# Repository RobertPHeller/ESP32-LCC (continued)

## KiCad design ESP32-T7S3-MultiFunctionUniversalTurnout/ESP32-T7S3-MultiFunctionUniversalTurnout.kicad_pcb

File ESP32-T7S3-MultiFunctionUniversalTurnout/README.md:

# ESP32-T7S3-MultiFunctionUniversalTurnout

This is a LCC node circuit board that is based around an Lily Go TTGO-T7S3
(Mini32) board to manage and operate a collection of model railroad sensors and
actuators. 

The board contains these I/O sections:

- Four occupancy detectors. CT Coil type sensors, so they won't work with DC
systems without an AC bias.
- Four turnout drivers with point sense.  These are on a daughter board.  There
are four daughter board types: one for stall motors (Tortoise and the like),
one for single-coil motors (Kato), one for twin-coil motors (Atlas, Peco), and
one for servos.
- Four Schmitt Trigger inputs, meant for push buttons.
- Four Buffered outputs, by default for Panel LEDS, but with drop in
resistors, can also drive relays or other loads.
- Sixteen PWM Led drivers. These are meant to light (LED) lamps in signal
heads.

The board connects to a LCC network and utilizes the Event Transport Protocol
in its operation. It also uses a CDI to describe its configuration. It can be
configured with JMRI or other available LCC configuration tools.

The board draws about 100ma, plus load. There are 16 signal lamp outputs that
have 1.5K Ohm load resistors, this means about 8ma per LED. If all lamps are
on at full brightness, this comes to 128ma, although turning all 16 signal
lamps on full at a time is not likely to be prototypical, since most signal
aspects only light one lamp per head. There is a terminal block to optionally
supply external power for the signal lamps, as a way to reduce the load on the
LCC power bus. The buffered output section uses an external power source, so
does not add any load to the LCC power bus.

This board is a multi-purpose board that can be used in a number of
situations, including (but not limited to): one end of a siding, a yard or
terminal throat, ABS, and interlocking plants.</p>

## Firmware

The firmware for this board is [ESP32-S3-MultiFunctionOpenMRNIDF](https://github.com/RobertPHeller/ESP32-LCC/tree/master/ESP32-S3-MultiFunctionOpenMRNIDF).

## Kit booket

There is LaTeX source for the kit booklet in [KitBooklet](https://github.com/RobertPHeller/ESP32-LCC/tree/master/ESP32-T7S3-MultiFunctionUniversalTurnout/KitBooklet).

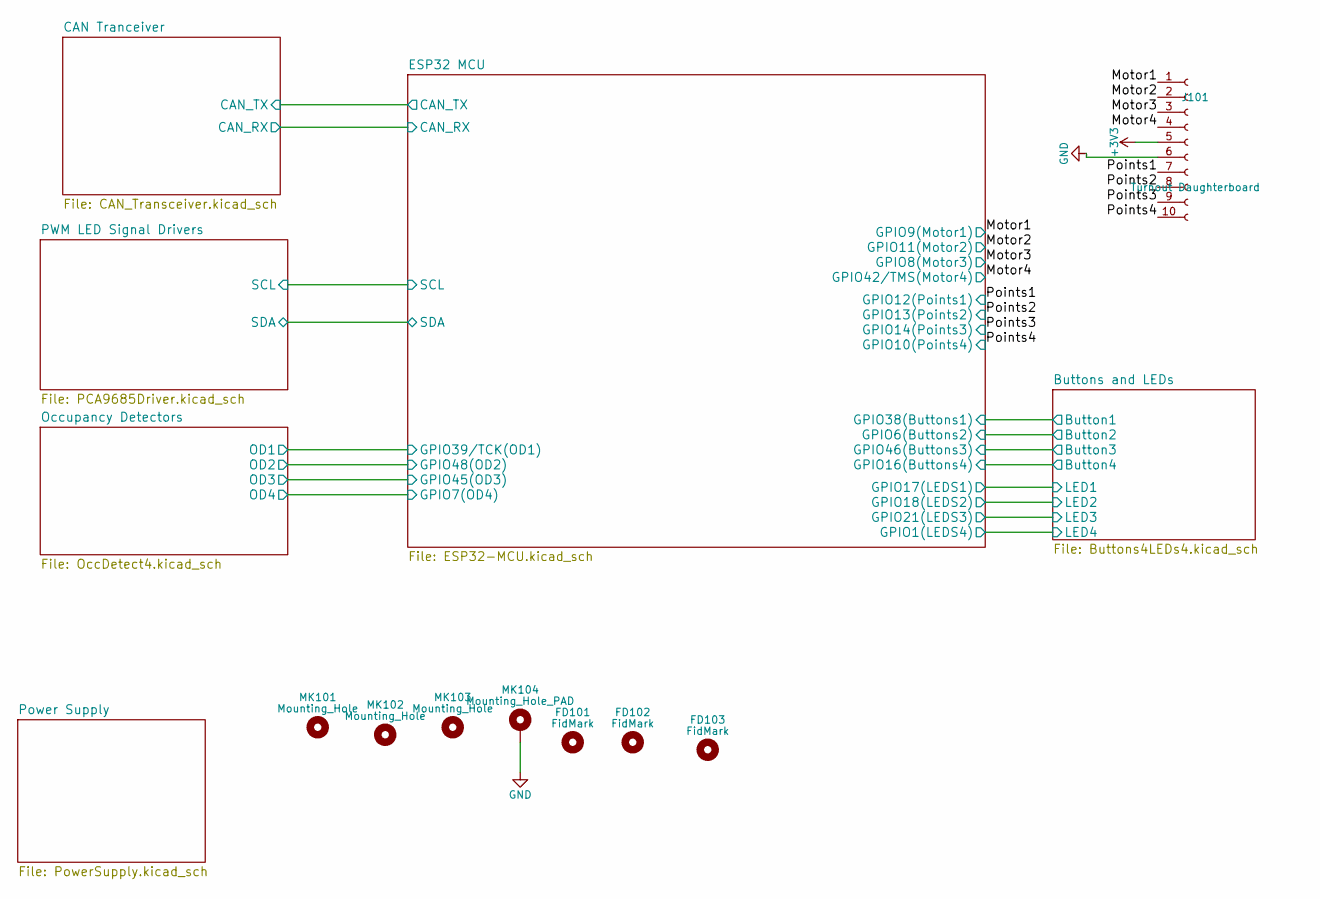
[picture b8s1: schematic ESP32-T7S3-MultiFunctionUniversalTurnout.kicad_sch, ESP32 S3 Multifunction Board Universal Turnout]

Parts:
FD101, FD102, FD103: FidMark; Fiducial_classic_Small_SilkscreenTop_Type1
J101: Turnout Daughterboard; Socket_Strip_Straight_1x10_Pitch2.54mm
MK101, MK102, MK103: Mounting_Hole; MountingHole_3.7mm
MK104: Mounting_Hole_PAD; MountingHole_3.7mm_Pad

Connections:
/Motor1: J101.1; also elsewhere on the board
/Motor2: J101.2; also elsewhere on the board
/Motor3: J101.3; also elsewhere on the board
/Motor4: J101.4; also elsewhere on the board
/Points1: J101.7; also elsewhere on the board
/Points2: J101.8; also elsewhere on the board
/Points3: J101.9; also elsewhere on the board
/Points4: J101.10; also elsewhere on the board
GND: J101.6, MK104.1; also elsewhere on the board

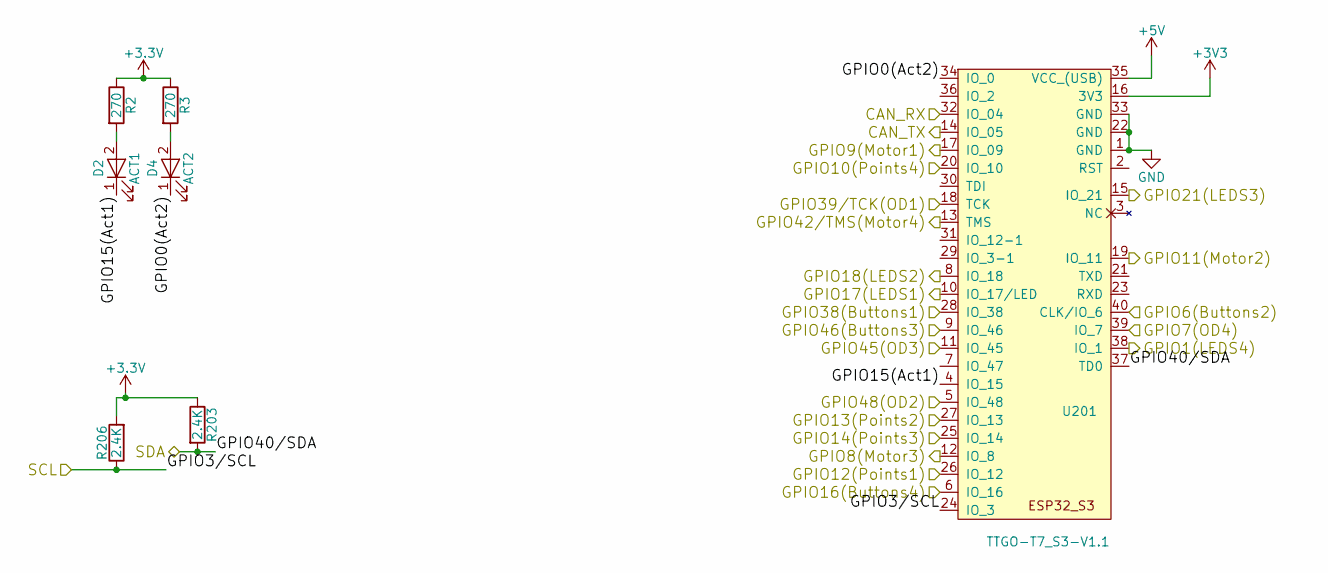
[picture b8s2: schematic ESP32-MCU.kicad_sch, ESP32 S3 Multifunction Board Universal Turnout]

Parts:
D2: ACT1; LED_0402; Mouser Part Number 710-150040GS73220
D4: ACT2; LED_0402; Mouser Part Number 710-150040SS73220
R2, R3: 270; R_0402; Mouser Part Number 754-RR0510P-271D
R203, R206: 2.4K; R_0402; Mouser Part Number 603-RC0402FR-072K4L
U201: TTGO-T7_S3-V1.1; ESP32_mini

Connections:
+5V: U201.35 (VCC_(USB)); also elsewhere on the board
/Buttons and LEDs/Button1: U201.28 (IO_38); also elsewhere on the board
/Buttons and LEDs/Button2: U201.40 (CLK/IO_6); also elsewhere on the board
/Buttons and LEDs/Button3: U201.9 (IO_46); also elsewhere on the board
/Buttons and LEDs/Button4: U201.6 (IO_16); also elsewhere on the board
/Buttons and LEDs/LED1: U201.10 (IO_17/LED); also elsewhere on the board
/Buttons and LEDs/LED2: U201.8 (IO_18); also elsewhere on the board
/Buttons and LEDs/LED3: U201.15 (IO_21); also elsewhere on the board
/Buttons and LEDs/LED4: U201.38 (IO_1); also elsewhere on the board
/CAN Tranceiver/CAN_RX: U201.32 (IO_04); also elsewhere on the board
/CAN Tranceiver/CAN_TX: U201.14 (IO_05); also elsewhere on the board
/ESP32 MCU/GPIO0(Act2): D4.1 (K), U201.34 (IO_0)
/ESP32 MCU/GPIO3/SCL: R206.1, U201.24 (IO_3); also elsewhere on the board
/ESP32 MCU/GPIO7(OD4): U201.39 (IO_7); also elsewhere on the board
/ESP32 MCU/GPIO15(Act1): D2.1 (K), U201.4 (IO_15)
/ESP32 MCU/GPIO39/TCK(OD1): U201.18 (TCK); also elsewhere on the board
/ESP32 MCU/GPIO40/SDA: R203.2, U201.37 (TD0); also elsewhere on the board
/ESP32 MCU/GPIO45(OD3): U201.11 (IO_45); also elsewhere on the board
/ESP32 MCU/GPIO48(OD2): U201.5 (IO_48); also elsewhere on the board
/Motor1: U201.17 (IO_09); also elsewhere on the board
/Motor2: U201.19 (IO_11); also elsewhere on the board
/Motor3: U201.12 (IO_8); also elsewhere on the board
/Motor4: U201.13 (TMS); also elsewhere on the board
/Points1: U201.26 (IO_12); also elsewhere on the board
/Points2: U201.27 (IO_13); also elsewhere on the board
/Points3: U201.25 (IO_14); also elsewhere on the board
/Points4: U201.20 (IO_10); also elsewhere on the board
GND: U201.1 (GND), U201.22 (GND), U201.33 (GND); also elsewhere on the board
unnamed: D2.2 (A), R2.2
unnamed: D4.2 (A), R3.2

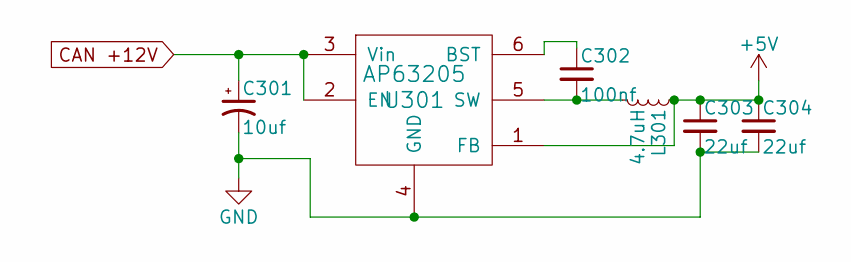
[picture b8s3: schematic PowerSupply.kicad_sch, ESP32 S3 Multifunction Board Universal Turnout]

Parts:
C301: 10uf; CP_Elec_5x5.3; Mouser Part Number 710-865230542002
C302: 100nf; C_0603; Mouser Part Number 710-885012206020
C303, C304: 22uf; C_0603; Mouser Part Number 603-CC0603MRX6S5B226
L301: 4.7uH; L_7.3x7.3_H4.5; Mouser Part Number 81-B1047AS-4R7N=P3
U301: AP63205; TSOT-23-6_MK06A; Mouser Part Number 621-AP63205WU-7

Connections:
+5V: C303.1, C304.1, L301.1, U301.1 (FB); also elsewhere on the board
CAN +12V: C301.1, U301.2 (EN), U301.3 (Vin); also elsewhere on the board
GND: C301.2, C303.2, C304.2, U301.4 (GND); also elsewhere on the board
unnamed: C302.1, U301.6 (BST)
unnamed: C302.2, L301.2, U301.5 (SW)

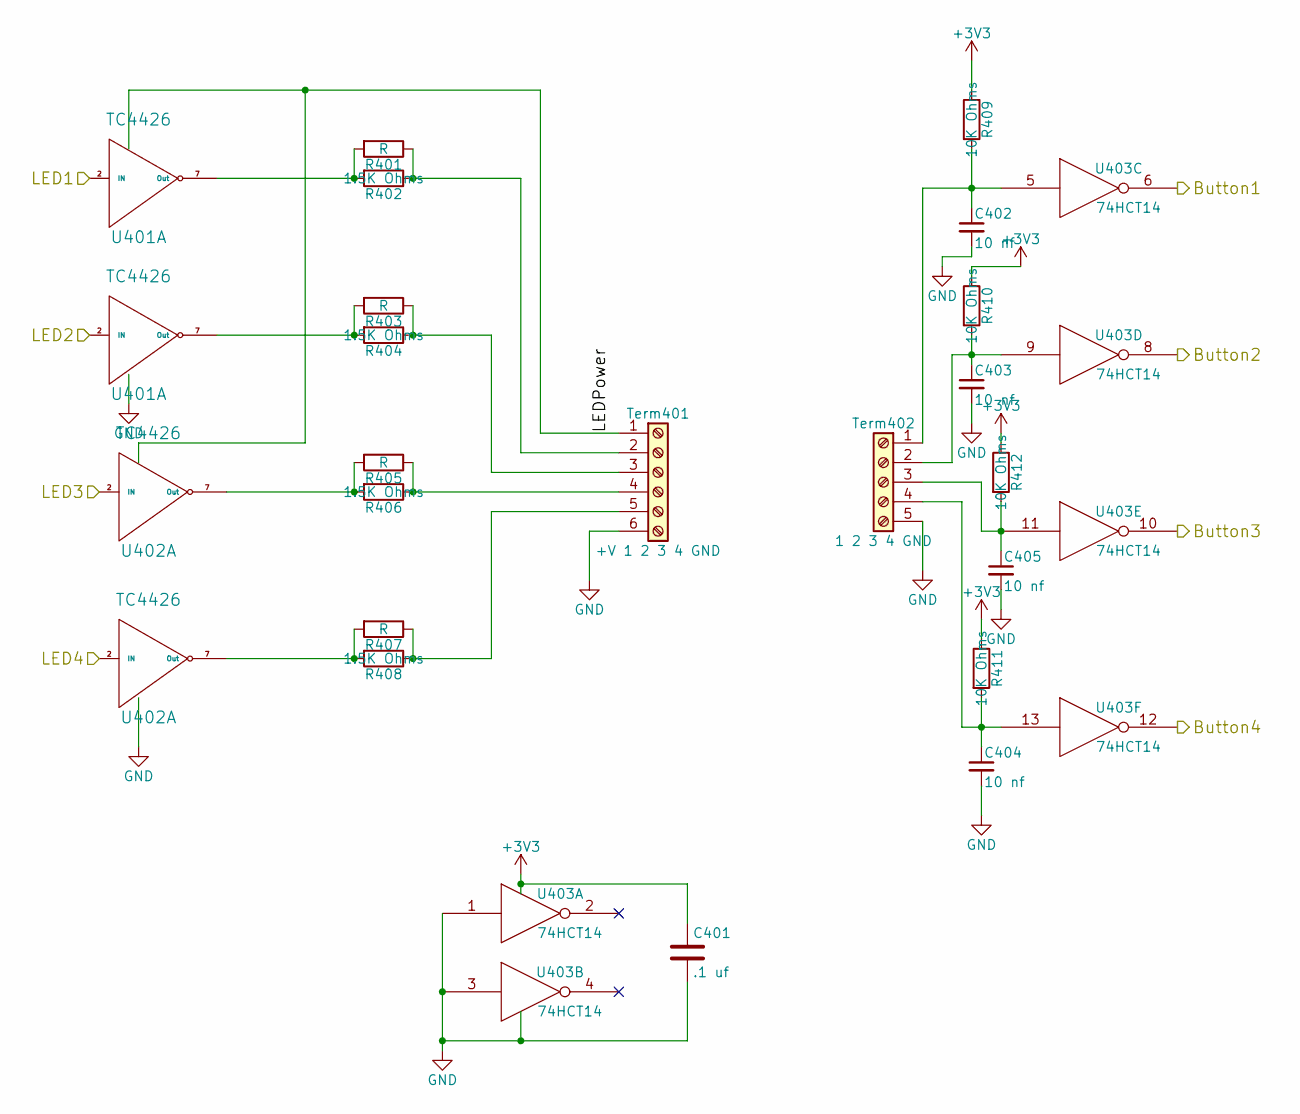
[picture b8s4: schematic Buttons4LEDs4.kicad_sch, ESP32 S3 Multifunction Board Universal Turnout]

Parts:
C401: .1 uf; C_0603; Mouser Part Number 710-885012206095
C402, C403, C404, C405: 10 nf; C_0603; Mouser Part Number 710-885382206002
R401, R403, R405, R407: R; R_Axial_DIN0207_L6.3mm_D2.5mm_P7.62mm_Horizontal
R402, R404, R406, R408: 1.5K Ohms; R_0603; Mouser Part Number 71-CRCW06031K50JNEAC
R409, R410, R411, R412: 10K Ohms; R_0603; Mouser Part Number 71-CRCW060310K0JNEBC
Term401: +V 1 2 3 4 GND; TerminalBlock_Pheonix_MPT-2.54mm_6pol; Mouser Part Number 651-1725698
Term402: 1 2 3 4 GND; TerminalBlock_Pheonix_MPT-2.54mm_5pol; Mouser Part Number 651-1725685
U401, U402: TC4426; SOIC-8_3.9x4.9mm_Pitch1.27mm; Mouser Part Number 579-TC1426COA713
U403: 74HCT14; SOIC-14_3.9x8.7mm_Pitch1.27mm; Mouser Part Number 595-CD74HC14M

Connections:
/Buttons and LEDs/Button1: U403.6; also elsewhere on the board
/Buttons and LEDs/Button2: U403.8; also elsewhere on the board
/Buttons and LEDs/Button3: U403.10; also elsewhere on the board
/Buttons and LEDs/Button4: U403.12; also elsewhere on the board
/Buttons and LEDs/LED1: U401.2 (IN); also elsewhere on the board
/Buttons and LEDs/LED2: U401.4 (IN); also elsewhere on the board
/Buttons and LEDs/LED3: U402.2 (IN); also elsewhere on the board
/Buttons and LEDs/LED4: U402.4 (IN); also elsewhere on the board
GND: C401.2, C402.2, C403.2, C404.2, C405.2, Term401.6, Term402.5, U401.3 (GND), U402.3 (GND), U403.1, U403.3, U403.7 (GND); also elsewhere on the board
unnamed: C402.1, R409.2, Term402.1, U403.5
unnamed: C403.1, R410.2, Term402.2, U403.9
unnamed: C404.1, R411.2, Term402.4, U403.13
unnamed: C405.1, R412.2, Term402.3, U403.11
unnamed: R401.1, R402.1, Term401.2
unnamed: R403.1, R404.1, Term401.3
unnamed: R405.1, R406.1, Term401.4
unnamed: R407.1, R408.1, Term401.5
VPower: Term401.1, U401.6 (VPower), U402.6 (VPower)

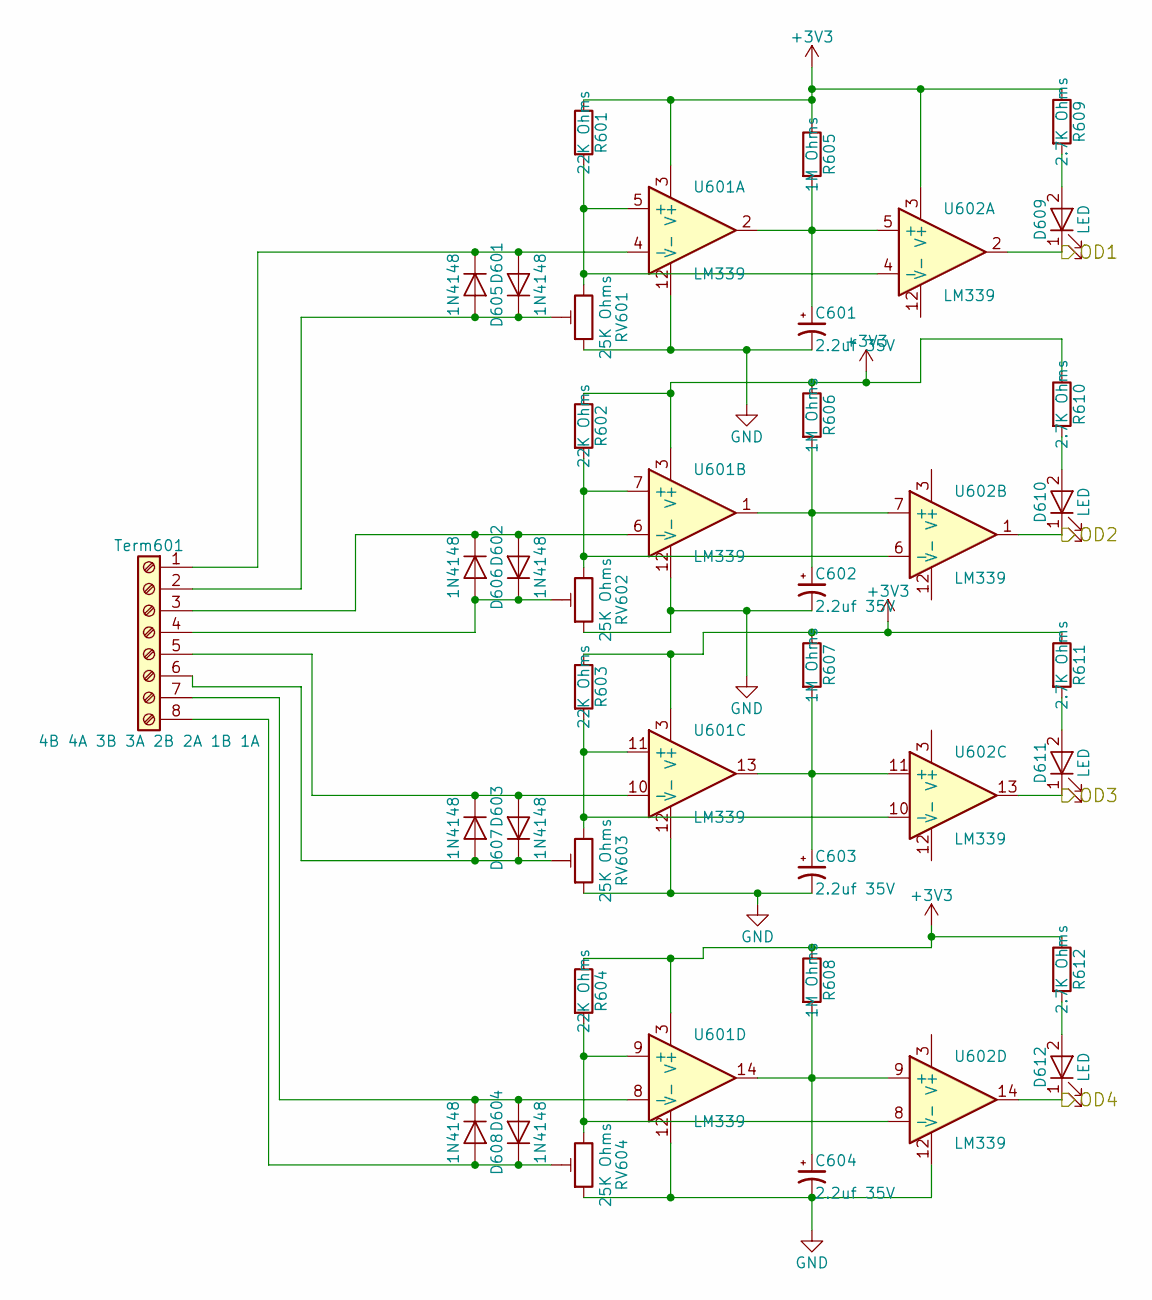
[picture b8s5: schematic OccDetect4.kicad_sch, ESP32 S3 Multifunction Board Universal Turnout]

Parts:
C601, C602, C603, C604: 2.2uf 35V; CP_Elec_4x5.7; Mouser Part Number 667-EEE-1VA2R2NR
D601, D602, D603, D604, D605, D606, D607, D608: 1N4148; D_SOD-323; Mouser Part Number 750-1N4148WS-HF
D609, D610, D611, D612: LED; LED_0603; Mouser Part Number 710-150060SS55040
R601, R602, R603, R604: 22K Ohms; R_0603; Mouser Part Number 71-RCG060322K0JNEA
R605, R606, R607, R608: 1M Ohms; R_0603; Mouser Part Number 71-CRCW06031M00JNEAC
R609, R610, R611, R612: 2.7K Ohms; R_0603; Mouser Part Number 71-CRCW06032K70JNEAC
RV601, RV602, RV603, RV604: 25K Ohms; Potentiometer_Trimmer_Bourns_3214J; Mouser Part Number 652-3314J-1-253E
Term601: 4B 4A 3B 3A 2B 2A 1B 1A; TerminalBlock_Pheonix_MPT-2.54mm_8pol; Mouser Part Number 651-1725711
U601, U602: LM339; SOIC-14_3.9x8.7mm_Pitch1.27mm; Mouser Part Number 595-LM339DR

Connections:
/ESP32 MCU/GPIO7(OD4): D612.1 (K), U602.14; also elsewhere on the board
/ESP32 MCU/GPIO39/TCK(OD1): D609.1 (K), U602.2; also elsewhere on the board
/ESP32 MCU/GPIO45(OD3): D611.1 (K), U602.13; also elsewhere on the board
/ESP32 MCU/GPIO48(OD2): D610.1 (K), U602.1; also elsewhere on the board
GND: C601.2, C602.2, C603.2, C604.2, RV601.1, RV602.1, RV603.1, RV604.1, U601.12 (V-), U602.12 (V-); also elsewhere on the board
unnamed: C601.1, R605.2, U601.2, U602.5 (+)
unnamed: C602.1, R606.2, U601.1, U602.7 (+)
unnamed: C603.1, R607.2, U601.13, U602.11 (+)
unnamed: C604.1, R608.2, U601.14, U602.9 (+)
unnamed: D601.1 (K), D605.2 (A), Term601.1, U601.4 (-)
unnamed: D601.2 (A), D605.1 (K), RV601.2, Term601.2
unnamed: D602.1 (K), D606.2 (A), Term601.3, U601.6 (-)
unnamed: D602.2 (A), D606.1 (K), RV602.2, Term601.4
unnamed: D603.1 (K), D607.2 (A), Term601.5, U601.10 (-)
unnamed: D603.2 (A), D607.1 (K), RV603.2, Term601.6
unnamed: D604.1 (K), D608.2 (A), Term601.7, U601.8 (-)
unnamed: D604.2 (A), D608.1 (K), RV604.2, Term601.8
unnamed: D609.2 (A), R609.2
unnamed: D610.2 (A), R610.2
unnamed: D611.2 (A), R611.2
unnamed: D612.2 (A), R612.2
unnamed: R601.2, RV601.3, U601.5 (+), U602.4 (-)
unnamed: R602.2, RV602.3, U601.7 (+), U602.6 (-)
unnamed: R603.2, RV603.3, U601.11 (+), U602.10 (-)
unnamed: R604.2, RV604.3, U601.9 (+), U602.8 (-)

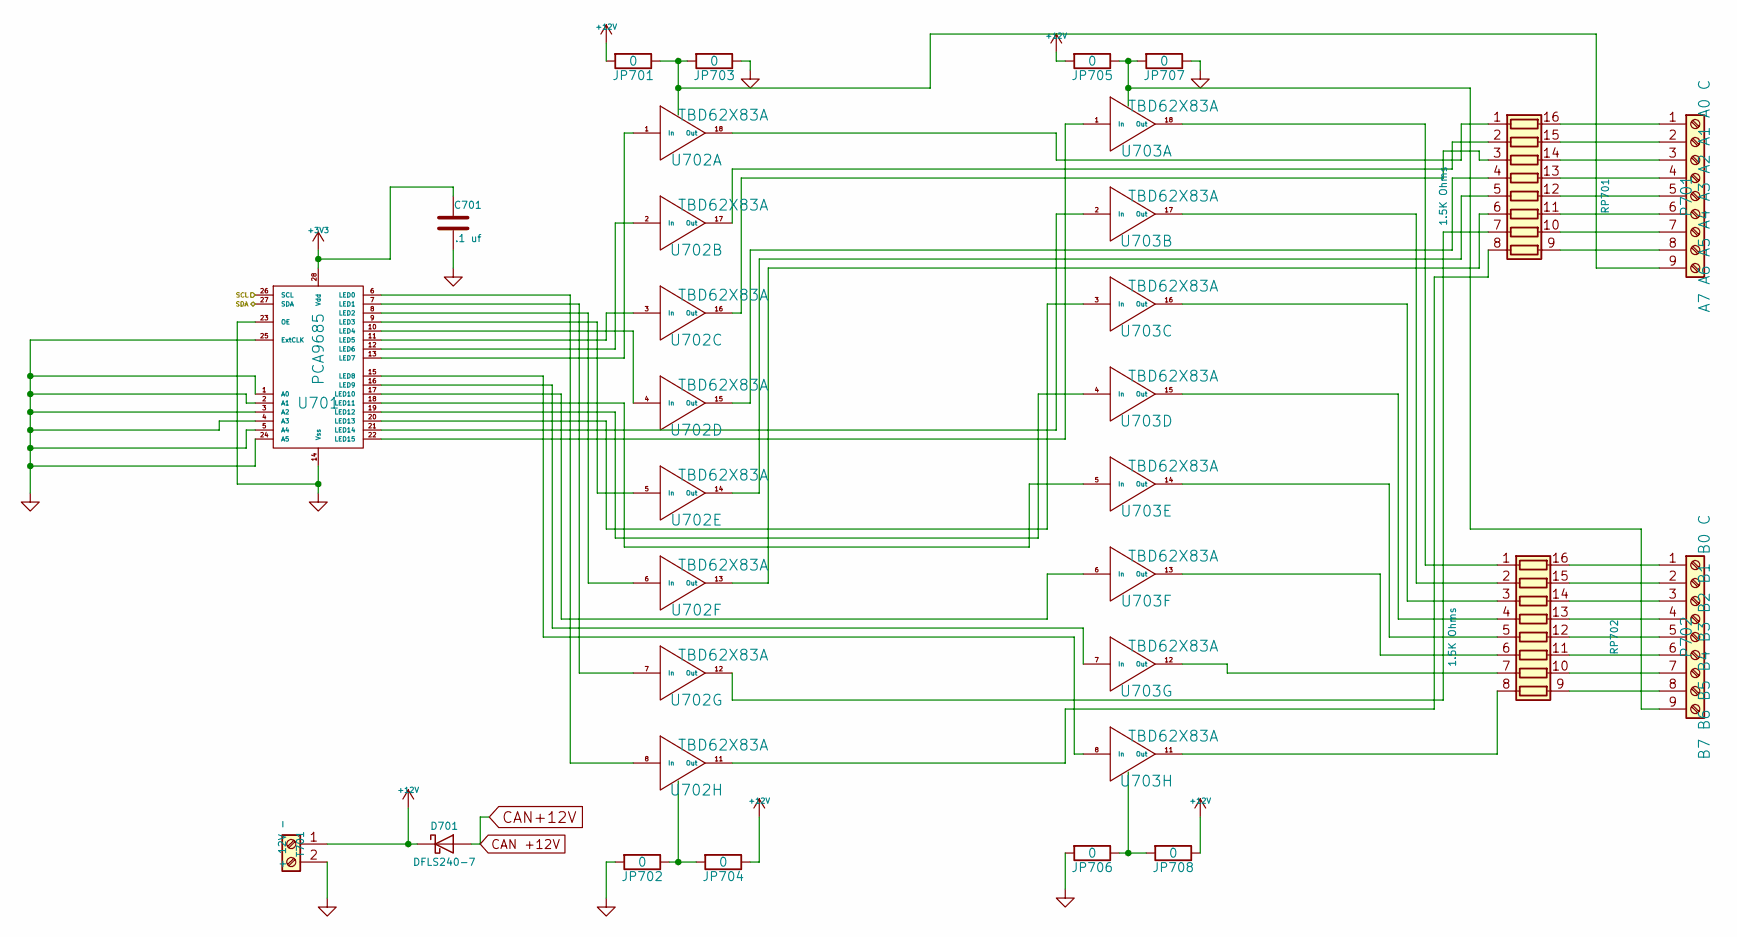
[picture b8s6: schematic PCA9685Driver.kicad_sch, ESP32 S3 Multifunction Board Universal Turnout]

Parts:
C701: .1 uf; C_0603; Mouser Part Number 710-885012206095
D701: DFLS240-7; D_PowerDI-123; Mouser Part Number 621-DFLS240-7
JP701, JP702, JP703, JP704, JP705, JP706, JP707, JP708: 0; R_1206; Mouser Part Number 71-CRCW12060000Z0EBC
P701: A7 A6 A5 A4 A3 A2 A1 A0 C; TerminalBlock_Pheonix_MPT-2.54mm_9pol; Mouser Part Number 651-1725724
P702: B7 B6 B5 B4 B3 B2 B1 B0 C; TerminalBlock_Pheonix_MPT-2.54mm_9pol; Mouser Part Number 651-1725724
RP701, RP702: 1.5K Ohms; 4816P; Mouser Part Number 652-4816P-T1LF-152LF
T701: + 12V -; TerminalBlock_Pheonix_MPT-2.54mm_2pol; Mouser Part Number 651-1725656
U701: PCA9685; TSSOP-28_4.4x9.7mm_Pitch0.65mm; Mouser Part Number 771-PCA9685PW,118
U702, U703: TBD62X83A; SOIC-18W_7.5x11.6mm_Pitch1.27mm; Mouser Part Number 757-TBD62083AFG or 757-TBD62783AFG

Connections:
+12V: D701.1 (K), JP701.2, JP704.1, JP705.2, JP708.1, T701.1
/ESP32 MCU/GPIO3/SCL: U701.26 (SCL); also elsewhere on the board
/ESP32 MCU/GPIO40/SDA: U701.27 (SDA); also elsewhere on the board
CAN +12V: D701.2 (A); also elsewhere on the board
GND: C701.2, JP702.2, JP703.1, JP706.2, JP707.1, T701.2, U701.1 (A0), U701.2 (A1), U701.3 (A2), U701.4 (A3), U701.5 (A4), U701.14 (Vss), U701.23 (OE), U701.24 (A5), U701.25 (ExtCLK); also elsewhere on the board
unnamed: JP701.1, JP703.2, P701.9, U702.10 (OC)
unnamed: JP702.1, JP704.2, U702.9 (IC)
unnamed: JP705.1, JP707.2, P702.9, U703.10 (OC)
unnamed: JP706.1, JP708.2, U703.9 (IC)
unnamed: P701.1, RP701.16 (R1.2)
unnamed: P701.2, RP701.15 (R2.2)
unnamed: P701.3, RP701.14 (R3.2)
unnamed: P701.4, RP701.13 (R4.2)
unnamed: P701.5, RP701.12 (R5.2)
unnamed: P701.6, RP701.11 (R6.2)
unnamed: P701.7, RP701.10 (R7.2)
unnamed: P701.8, RP701.9 (R8.2)
unnamed: P702.1, RP702.16 (R1.2)
unnamed: P702.2, RP702.15 (R2.2)
unnamed: P702.3, RP702.14 (R3.2)
unnamed: P702.4, RP702.13 (R4.2)
unnamed: P702.5, RP702.12 (R5.2)
unnamed: P702.6, RP702.11 (R6.2)
unnamed: P702.7, RP702.10 (R7.2)
unnamed: P702.8, RP702.9 (R8.2)
unnamed: RP701.1 (R1.1), U702.18 (Out)
unnamed: RP701.2 (R2.1), U702.17 (Out)
unnamed: RP701.3 (R3.1), U702.16 (Out)
unnamed: RP701.4 (R4.1), U702.15 (Out)
unnamed: RP701.5 (R5.1), U702.14 (Out)
unnamed: RP701.6 (R6.1), U702.13 (Out)
unnamed: RP701.7 (R7.1), U702.12 (Out)
unnamed: RP701.8 (R8.1), U702.11 (Out)
unnamed: RP702.1 (R1.1), U703.18 (Out)
unnamed: RP702.2 (R2.1), U703.17 (Out)
unnamed: RP702.3 (R3.1), U703.16 (Out)
unnamed: RP702.4 (R4.1), U703.15 (Out)
unnamed: RP702.5 (R5.1), U703.14 (Out)
unnamed: RP702.6 (R6.1), U703.13 (Out)
unnamed: RP702.7 (R7.1), U703.12 (Out)
unnamed: RP702.8 (R8.1), U703.11 (Out)
unnamed: U701.6 (LED0), U702.8 (In)
unnamed: U701.7 (LED1), U702.7 (In)
unnamed: U701.8 (LED2), U702.6 (In)
unnamed: U701.9 (LED3), U702.5 (In)
unnamed: U701.10 (LED4), U702.4 (In)
unnamed: U701.11 (LED5), U702.3 (In)
unnamed: U701.12 (LED6), U702.2 (In)
unnamed: U701.13 (LED7), U702.1 (In)
unnamed: U701.15 (LED8), U703.8 (In)
unnamed: U701.16 (LED9), U703.7 (In)
unnamed: U701.17 (LED10), U703.6 (In)
unnamed: U701.18 (LED11), U703.5 (In)
unnamed: U701.19 (LED12), U703.4 (In)
unnamed: U701.20 (LED13), U703.3 (In)
unnamed: U701.21 (LED14), U703.2 (In)
unnamed: U701.22 (LED15), U703.1 (In)

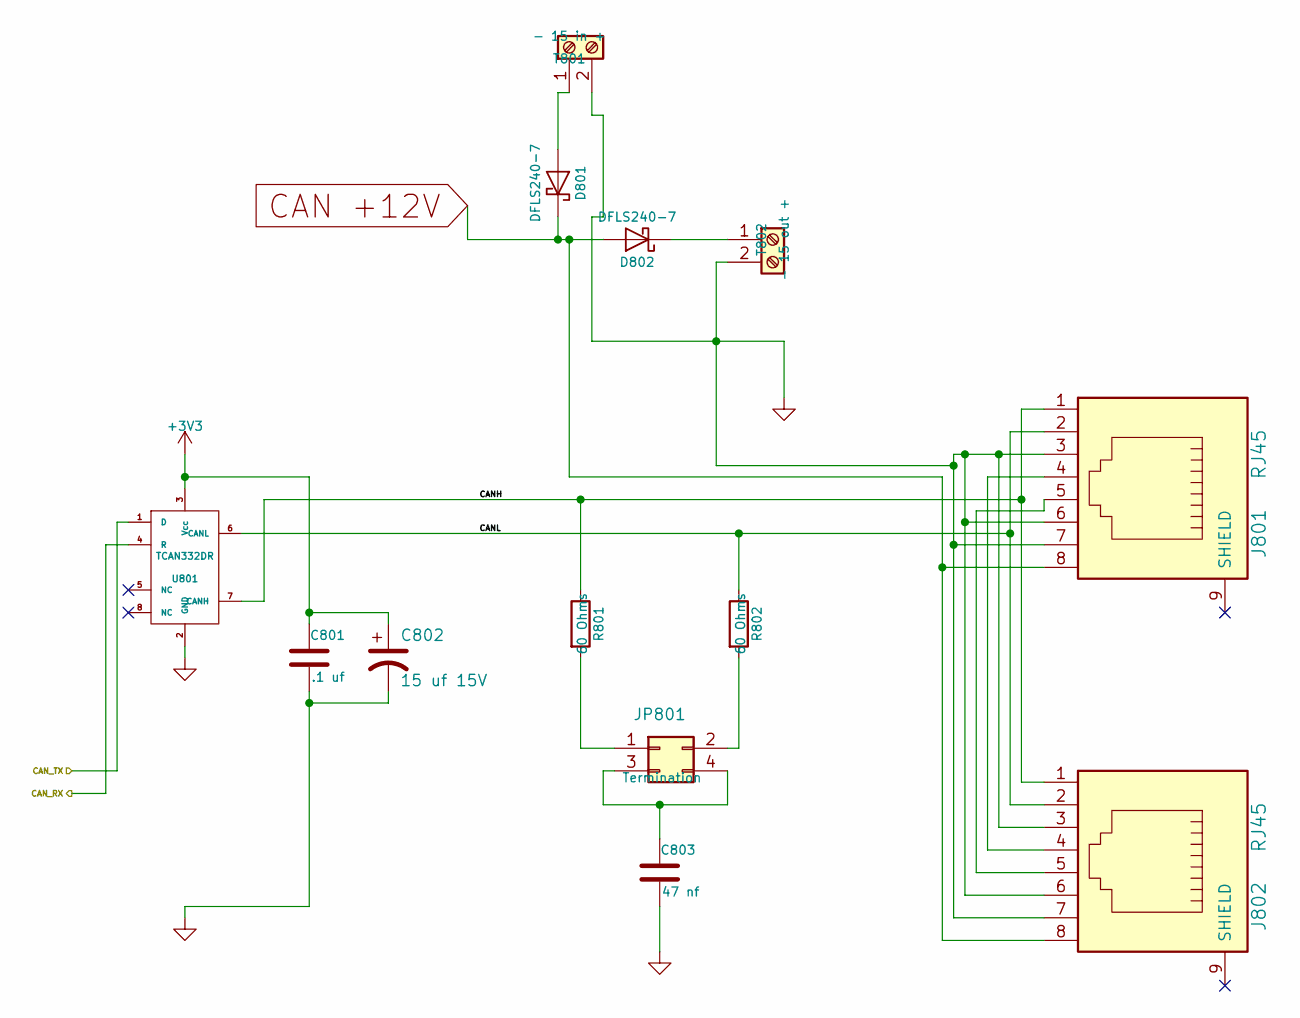
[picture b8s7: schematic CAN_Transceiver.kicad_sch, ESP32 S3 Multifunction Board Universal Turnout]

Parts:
C801: .1 uf; C_0603; Mouser Part Number 710-885012206095
C802: 15 uf 15V; CP_Elec_4x5.7; Mouser Part Number 710-865080340002
C803: 47 nf; C_0603; Mouser Part Number 710-885012206093
D801, D802: DFLS240-7; D_PowerDI-123; Mouser Part Number 621-DFLS240-7
J801, J802: RJ45; RJ45_8N-S; Mouser Part Number 710-615008144221
JP801: Termination; Pin_Header_Straight_2x02_Pitch2.54mm; Mouser Part Number 649-67997-404HLF
R801, R802: 60 Ohms; R_1206; Mouser Part Number 71-CRCW120660R0KNAIF
T801: - 15 in +; TerminalBlock_Pheonix_MPT-2.54mm_2pol; Mouser Part Number 651-1725656
T802: - 15 out +; TerminalBlock_Pheonix_MPT-2.54mm_2pol; Mouser Part Number 651-1725656
U801: TCAN332DR; SOIC-8_3.9x4.9mm_Pitch1.27mm; Mouser Part Number 595-TCAN332DR

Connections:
/CAN Tranceiver/CANH: J801.1, J802.1, R801.1, U801.7 (CANH)
/CAN Tranceiver/CANL: J801.2, J802.2, R802.1, U801.6 (CANL)
/CAN Tranceiver/CAN_RX: U801.4 (R); also elsewhere on the board
/CAN Tranceiver/CAN_TX: U801.1 (D); also elsewhere on the board
CAN +12V: D801.1 (K), D802.2 (A), J801.8, J802.8; also elsewhere on the board
GND: C801.2, C802.2, C803.2, J801.3, J801.6, J801.7, J802.3, J802.6, J802.7, T801.2, T802.2, U801.2 (GND); also elsewhere on the board
unnamed: C803.1, JP801.3, JP801.4
unnamed: D801.2 (A), T801.1
unnamed: D802.1 (K), T802.1
unnamed: J801.4, J802.4
unnamed: J801.5, J802.5
unnamed: JP801.1, R801.2
unnamed: JP801.2, R802.2

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
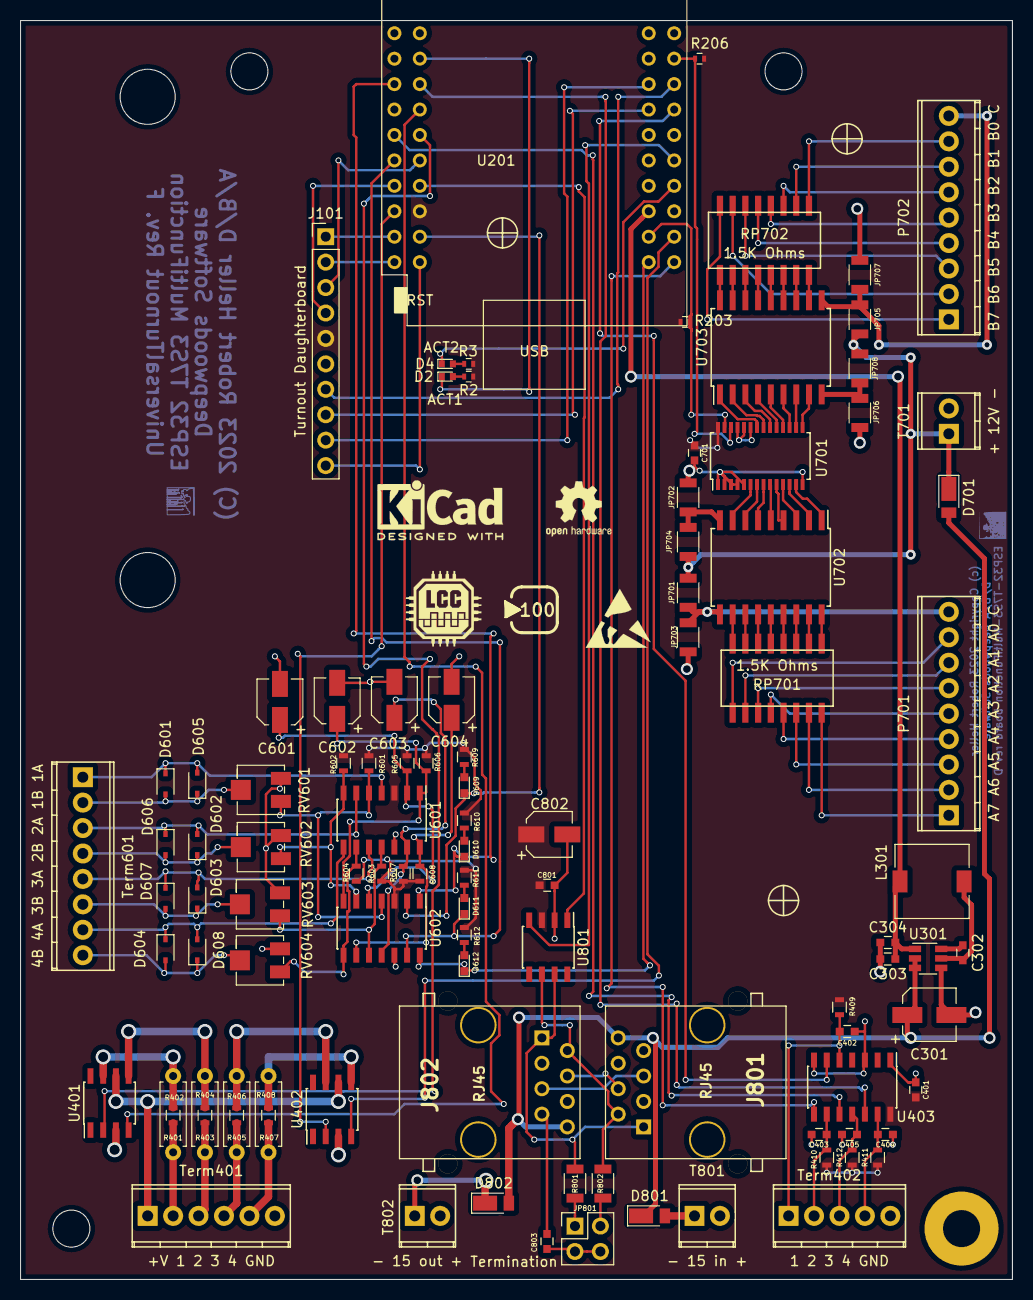
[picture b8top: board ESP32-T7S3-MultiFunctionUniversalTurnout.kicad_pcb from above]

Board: 2 copper layers, 99.1 x 125.7 mm, 109 parts (0 on the bottom side), 129 nets.

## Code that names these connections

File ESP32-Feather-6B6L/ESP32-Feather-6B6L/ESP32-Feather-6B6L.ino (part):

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#if defined(USE_TWAI)
/// This is the ESP32-S3 pin connected to the CAN Transceiver Rx
/// Assumes Adafruit ESP32-S3 Feather: GPIOA4 == GPIO14
constexpr gpio_num_t CAN_RX_PIN = GPIO_NUM_14;

/// This is the ESP32 pin connected to the  CAN Transceiver Tx
/// Assumes Adafruit ESP32-S3 Feather: GPIOA5 == GPIO8
constexpr gpio_num_t CAN_TX_PIN = GPIO_NUM_8; 

#endif // USE_CAN or USE_TWAI

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#endif // USE_WIFI

#if defined(USE_TWAI)
Esp32HardwareTwai twai(CAN_RX_PIN, CAN_TX_PIN);
#endif // USE_TWAI

// Declare output pins.  
GPIO_PIN(LED1, GpioOutputSafeLow, 13); // GPIO13
GPIO_PIN(LED2, GpioOutputSafeLow, 12); // GPIO12
GPIO_PIN(LED3, GpioOutputSafeLow, 11); // GPIO11
GPIO_PIN(LED4, GpioOutputSafeLow, 10); // GPIO10
GPIO_PIN(LED5, GpioOutputSafeLow,  9); // GPIO9
GPIO_PIN(LED6, GpioOutputSafeLow,  6); // GPIO6
GPIO_PIN(LED7, GpioOutputSafeLow,  5); // GPIO5
GPIO_PIN(LED8, GpioOutputSafeLow, 37); // GPIOMISO

// Declare input pins                                                           
GPIO_PIN(Button1, GpioInputPU, 18); // GPIOA0
GPIO_PIN(Button2, GpioInputPU, 17); // GPIOA1
GPIO_PIN(Button3, GpioInputPU, 16); // GPIOA2
GPIO_PIN(Button4, GpioInputPU, 15); // GPIOA3
GPIO_PIN(Button5, GpioInputPU, 36); // GPIOASCK
GPIO_PIN(Button6, GpioInputPU, 35); // GPIOAMOSI

LED led1(openmrn.stack()->node(), cfg.seg().leds().entry<0>(), LED1_Pin());
LED led2(openmrn.stack()->node(), cfg.seg().leds().entry<1>(), LED2_Pin());
LED led3(openmrn.stack()->node(), cfg.seg().leds().entry<2>(), LED3_Pin());
LED led4(openmrn.stack()->node(), cfg.seg().leds().entry<3>(), LED4_Pin());
LED led5(openmrn.stack()->node(), cfg.seg().leds().entry<4>(), LED5_Pin());
LED led6(openmrn.stack()->node(), cfg.seg().leds().entry<5>(), LED6_Pin());
LED led7(openmrn.stack()->node(), cfg.seg().leds().entry<6>(), LED7_Pin());
LED led8(openmrn.stack()->node(), cfg.seg().leds().entry<7>(), LED8_Pin());

Button button1(openmrn.stack()->node(), cfg.seg().buttons().entry<0>(), Button1_Pin());
Button button2(openmrn.stack()->node(), cfg.seg().buttons().entry<1>(), Button2_Pin());
Button button3(openmrn.stack()->node(), cfg.seg().buttons().entry<2>(), Button3_Pin());
Button button4(openmrn.stack()->node(), cfg.seg().buttons().entry<3>(), Button4_Pin());
Button button5(openmrn.stack()->node(), cfg.seg().buttons().entry<4>(), Button5_Pin());
Button button6(openmrn.stack()->node(), cfg.seg().buttons().entry<5>(), Button6_Pin());

// Create an initializer that can initialize all the GPIO pins in one shot
typedef GpioInitializer<
LED1_Pin, LED2_Pin, LED3_Pin, LED4_Pin, LED5_Pin, LED6_Pin, LED7_Pin, 
LED8_Pin, Button1_Pin, Button2_Pin, Button3_Pin, Button4_Pin, Button5_Pin, 
Button1_Pin> GpioInit;

// The producers need to be polled repeatedly for changes and to execute the
// debouncing algorithm. This class instantiates a refreshloop and adds the
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    // before we startup the OpenMRN stack.
    if (request_bootloader())
    {
        esp32_bootloader_run(NODE_ID, CAN_RX_PIN, CAN_TX_PIN);
        // This line should not be reached as the esp32_bootloader_run method
        // will not return by default.
        HASSERT(false);
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
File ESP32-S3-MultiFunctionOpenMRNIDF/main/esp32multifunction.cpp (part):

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        ServoTurnout turnout3(stack.node(), cfg.seg().turnouts().entry<2>(),1000,ledc.get_channel(2));
        ServoTurnout turnout4(stack.node(), cfg.seg().turnouts().entry<3>(),1000,ledc.get_channel(3));
#else
        Turnout turnout1(stack.node(), cfg.seg().turnouts().entry<0>(),Motor1_Pin());
        Turnout turnout2(stack.node(), cfg.seg().turnouts().entry<1>(),Motor2_Pin());
        Turnout turnout3(stack.node(), cfg.seg().turnouts().entry<2>(),Motor3_Pin());
        Turnout turnout4(stack.node(), cfg.seg().turnouts().entry<3>(),Motor4_Pin());
#endif
        LOG(INFO, "[esp32multifunction] Turnouts done.");
        Points points1(stack.node(), cfg.seg().points().entry<0>(),Points1_Pin());
        Points points2(stack.node(), cfg.seg().points().entry<1>(),Points2_Pin());
        Points points3(stack.node(), cfg.seg().points().entry<2>(),Points3_Pin());
        Points points4(stack.node(), cfg.seg().points().entry<3>(),Points4_Pin());
        LOG(INFO, "[esp32multifunction] Points done.");
        OccupancyDetector od1(stack.node(), cfg.seg().ocs().entry<0>(),OD1_Pin());
        OccupancyDetector od2(stack.node(), cfg.seg().ocs().entry<1>(),OD2_Pin());
        OccupancyDetector od3(stack.node(), cfg.seg().ocs().entry<2>(),OD3_Pin());
        OccupancyDetector od4(stack.node(), cfg.seg().ocs().entry<3>(),OD4_Pin());
        LOG(INFO, "[esp32multifunction] OccupancyDetector done."); 
        Button button1(stack.node(), cfg.seg().buttons().entry<0>(),Button1_Pin());
        Button button2(stack.node(), cfg.seg().buttons().entry<1>(),Button2_Pin());
        Button button3(stack.node(), cfg.seg().buttons().entry<2>(),Button3_Pin());
        Button button4(stack.node(), cfg.seg().buttons().entry<3>(),Button4_Pin());
        LOG(INFO, "[esp32multifunction] Buttons done.");
        LED Led1(stack.node(), cfg.seg().leds().entry<0>(),LED1_Pin());
        LED Led2(stack.node(), cfg.seg().leds().entry<1>(),LED2_Pin());
        LED Led3(stack.node(), cfg.seg().leds().entry<2>(),LED3_Pin());
        LED Led4(stack.node(), cfg.seg().leds().entry<3>(),LED4_Pin());
        LOG(INFO, "[esp32multifunction] LEDs done.");
        openlcb::RefreshLoop points_refresh_loop(stack.node(),{
                                                 points1.polling()
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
